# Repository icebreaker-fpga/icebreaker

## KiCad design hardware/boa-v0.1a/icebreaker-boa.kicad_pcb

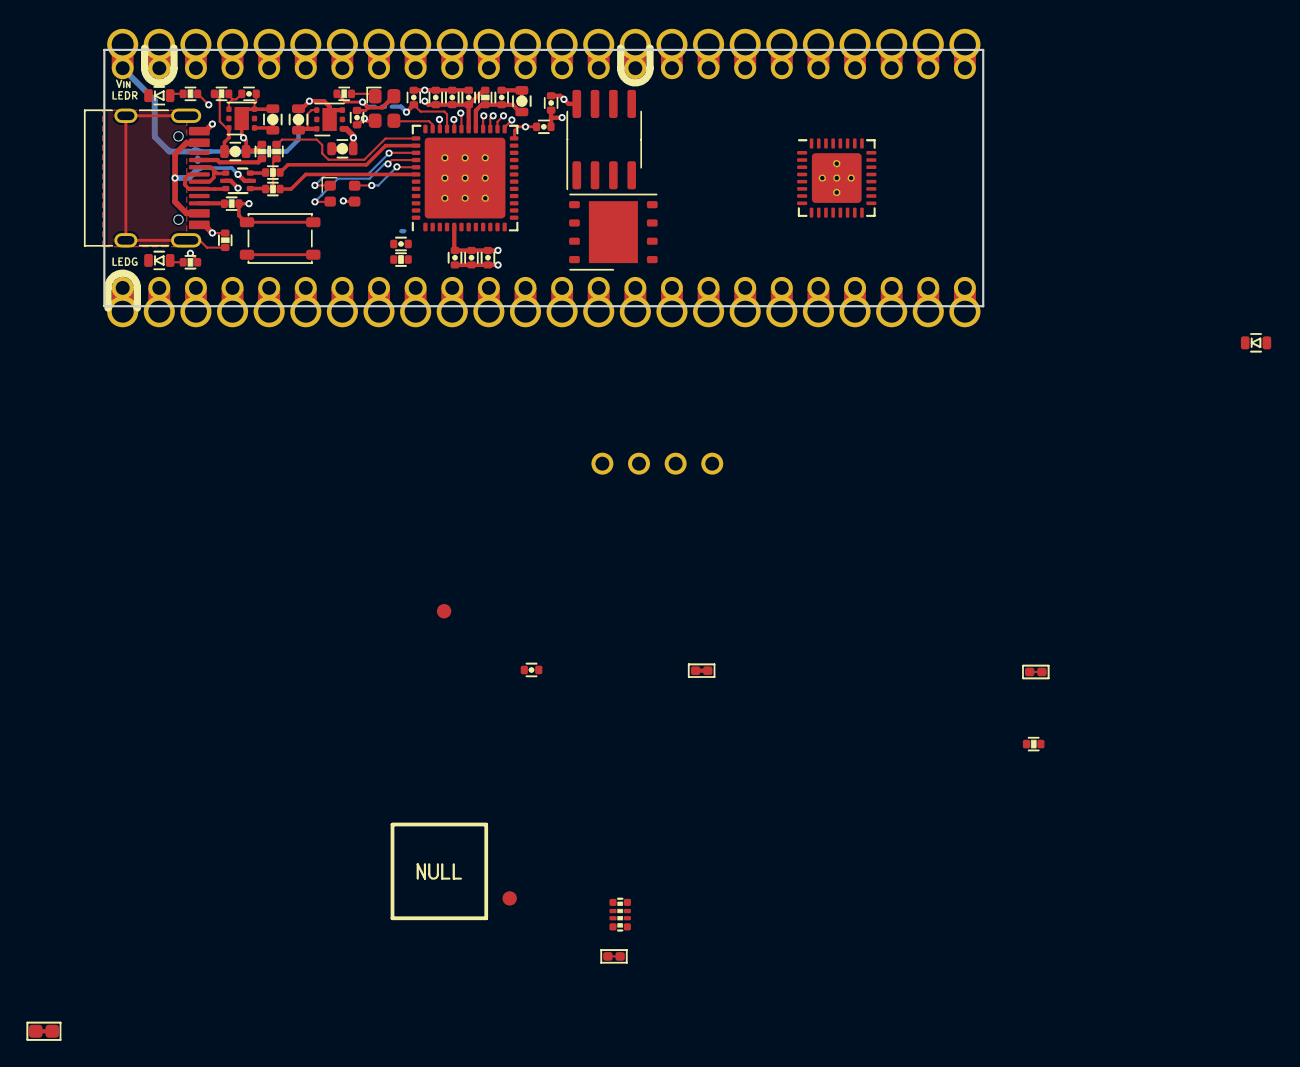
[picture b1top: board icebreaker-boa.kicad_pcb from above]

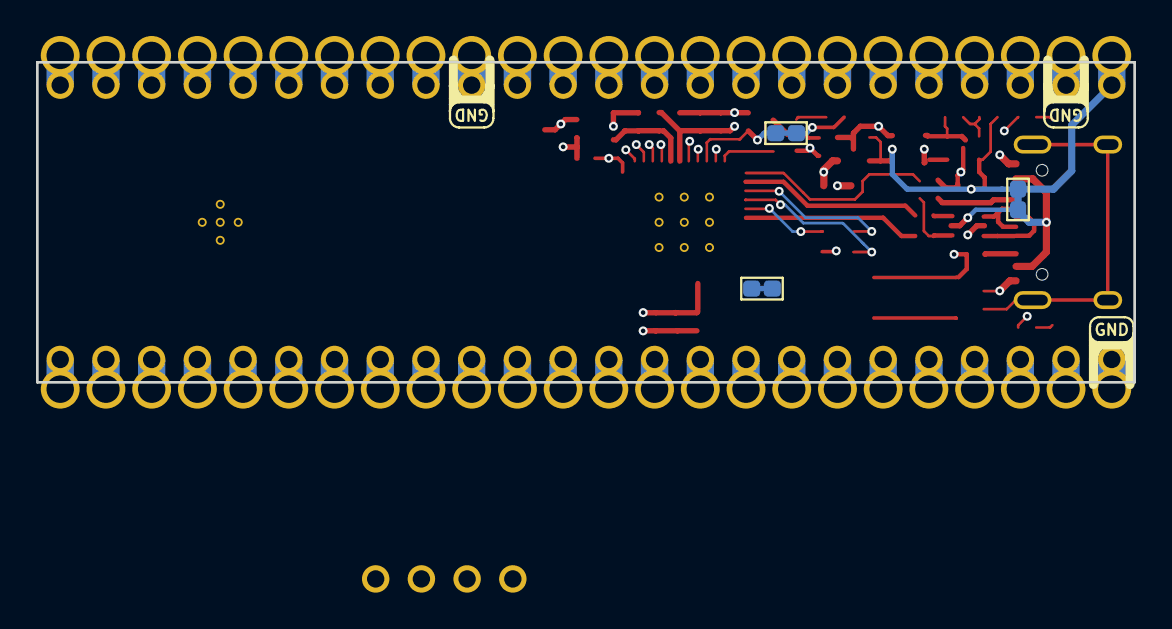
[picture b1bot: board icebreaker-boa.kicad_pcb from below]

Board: 4 copper layers, 61.0 x 17.8 mm, 109 parts (3 on the bottom side), 41 nets.

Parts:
C1, C9, C14: 1u; C_0402
C2, C3, C4, C5: 4u7; C_0603
C6, C7, C8, C11, C12, C15, C17, C18, C19: 100n; C_0402
C10: 10u; C_0603
C13, C16: 10n; C_0402
D1: RED; D_0603
D2: GRN; D_0603
D3: BLU; D_0603
D4: FM-B2020RGBA-HG; LED_TRI_2020
J1: USB_C; USB_C_Receptacle_HRO_TYPE-C-31-M-12
JP1: Jumper; J_NC_0603_40
JP2, JP3: Jumper; J_NC_0402_15
JP4, JP6, JP7: Jumper; J_NC_0603_30
JP5: Jumper; J_NC_0402_30
LOGO1: 1BitSquared; null_Logo_SilkS_6.5mm
P1, P2, P3, P4, P5, P6, P7, P8, P9, P10, P11, P12, P13, P14, P15, P16, P17, P18, P19, P20, P21, P22, P23, P24, P25, P26, P27, P28, P29, P30, P31, P32, P33, P34, P35, P42, P43, P44, P45, P46, P47, P48, P49, P50, P51, P52, P53, P54: ?; Pin_Header_Straight_Round_1x01_Castellated
P36: CS; Pin_Header_Straight_Round_1x01
P37: SCK; Pin_Header_Straight_Round_1x01
P38: MISO; Pin_Header_Straight_Round_1x01
P39: MOSI; Pin_Header_Straight_Round_1x01
P40: IO3; PAD_SMD_R_1x1
P41: IO2; PAD_SMD_R_1x1
R1: 1M; R_0402
R2, R3: 5k1; R_0402
R4, R5: 22E; R_0402
R6: 1k5; R_0402
R7, R8, R10: 10k; R_0402
R9: 10k; R_Array_Convex_4x0402
R11, R12, R13: 2k2; R_0402
R14: 100E; R_0402
SW1: TACT; SW_SPST_3x4x2.5
U1: USBLC6-2; SOT-666
U2: TLV75533PDRV; WSON-6-1EP_2x2mm_P0.65mm_EP1x1.6mm
U3: TLV73312PDRV; WSON-6-1EP_2x2mm_P0.65mm_EP1x1.6mm
U4: LY68L6400; SOIC-8_3.9x4.9mm_P1.27mm
U5: W25Q128JVxxM; WSON-8-1EP_6x5mm_P1.27mm_EP3.4x4.3mm
U6: ICE40UP5K-SG48; QFN-48-1EP_7x7mm_Pitch0.5mm
U7: ESP32-C3; QFN-32-1EP_5x5mm_Pitch0.5mm
X1: 12MHz; Oscillator_SMD_SCTF_S2DXX-4Pin_2.5x2.0mm

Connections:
+1V2: C5.1, C9.1, C11.1, C13.1, C14.1, C15.1, C16.1, R14.2, U3.1, U6.5, U6.30
+3V3: C3.1, C6.1, C7.1, C19.1, D4.3, JP4.2, JP5.1, JP6.2, JP7.2, P15.1, P50.1, R8.1, R9.1, R9.3, R9.6, R9.8, R11.2, R12.2, R13.2, U2.1, U4.8, U5.8, U6.22, U7.2, U7.3, U7.11, U7.17, U7.18, X1.4
/3V3_EN: C1.1, R7.2, U2.4
/AREF: JP7.1, U7.31, U7.32
/CC1: J1.A5, R2.2
/CC2: J1.B5, R3.2
/CDONE: D3.A, R13.1, U6.7
/CLK: U6.35, X1.3
/CLK_EN: R8.2, X1.1
/FLASH_~CS: JP3.1, R9.4, U5.1
/FPGA/VCCPLL: C10.1, C12.1, R14.1, U6.29
/FPGA/VPP_2V5: C17.1, JP5.2, U6.24
/IOB_13b-~LEDG: D2.C, JP2.2, U6.6
/IOT_36b-~LEDR: D1.C, U6.25
/RAM_~CS: JP2.1, R9.7, U4.1
/SHIELD: J1.S1, R1.2
/SPI_MISO-IO1: P38.1, U4.2, U5.2, U6.17
/SPI_MOSI-IO0: P39.1, U4.5, U5.5, U6.14
/SPI_SCK: P37.1, R9.2, U4.6, U5.6, U6.15
/SPI_~CS: JP3.2, P36.1, U6.16
/SPI_~HLD~-IO3: P40.1, U4.7, U5.7, U6.19
/SPI_~WP~-IO2: P41.1, U4.3, U5.3, U6.18
/USB_DET: R6.1, U6.37
/USB_N: R4.1, U6.38
/USB_P: R5.1, U6.42
/VCCIO_0: C18.1, JP6.1, U6.33
/VCCIO_2: C8.1, JP4.1, R10.2, U6.1
/iD+: R5.2, R6.2, U1.4
/iD-: R4.2, U1.6
/xD+: J1.A6, J1.B6, U1.3
/xD-: J1.A7, J1.B7, U1.1
/~BTN: R10.1, SW1.2, U6.2
/~CRESET: R9.5, U6.8
/~RGB0: D4.1, U6.39
/~RGB1: D4.4, U6.40
/~RGB2: D4.2, U6.41
GND: C1.2, C2.2, C3.2, C4.2, C5.2, C6.2, C7.2, C8.2, C9.2, C10.2, C11.2, C12.2, C13.2, C14.2, C15.2, C16.2, C17.2, C18.2, C19.2, D3.C, J1.A1, J1.A12, J1.B1, J1.B12, P1.1, P46.1, P53.1, R1.1, R2.1, R3.1, SW1.1, U1.2, U2.3, U2.7, U3.3, U3.7, U4.4, U5.4, U6.49, U7.33, X1.2
unnamed: D1.A, R11.1
unnamed: D2.A, R12.1
VBUS: J1.A4, J1.A9, J1.B4, J1.B9, JP1.1, U1.5
VIN: C2.1, C4.1, JP1.2, P4.1, R7.1, U2.6, U3.4, U3.6

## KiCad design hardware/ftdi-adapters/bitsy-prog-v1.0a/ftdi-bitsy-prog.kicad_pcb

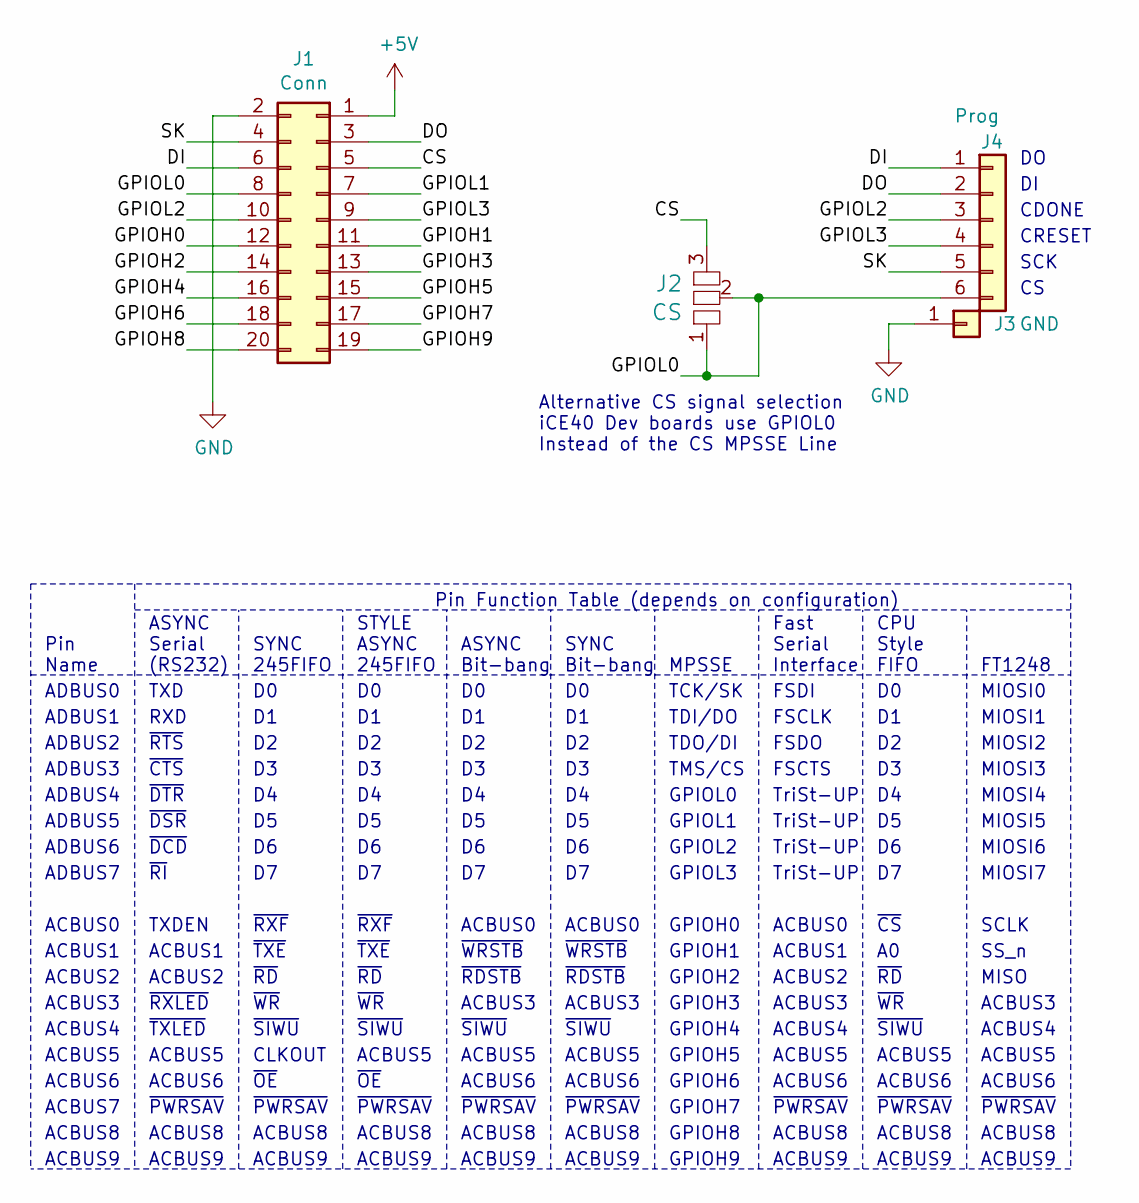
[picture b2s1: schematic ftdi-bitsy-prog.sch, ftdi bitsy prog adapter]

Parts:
J1: Conn; FTSH-EDGE-20pin
J2: CS; J_0602
J3: GND; PinSocket_1x01_P2.54mm_Vertical
J4: Prog; PinSocket_1x06_P2.54mm_Vertical

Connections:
+5V: J1.1
/CS: J1.5, J2.3
/DI: J1.6, J4.1
/DO: J1.3, J4.2
/GPIOH0: J1.12
/GPIOH1: J1.11
/GPIOH2: J1.14
/GPIOH3: J1.13
/GPIOH4: J1.16
/GPIOH5: J1.15
/GPIOH6: J1.18
/GPIOH7: J1.17
/GPIOH8: J1.20
/GPIOH9: J1.19
/GPIOL0: J1.8, J2.1, J2.2, J4.6
/GPIOL1: J1.7
/GPIOL2: J1.10, J4.3
/GPIOL3: J1.9, J4.4
/SK: J1.4, J4.5
GND: J1.2, J3.1

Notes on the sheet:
STYLE ASYNC 245FIFO
~RXF
~TXE
~RD
~WR
~SIWU
ACBUS5
~OE
~PWRSAV
ACBUS8
ACBUS9
ASYNC Bit-bang
ACBUS0
~WRSTB
~RDSTB
ACBUS3
ACBUS6
SYNC Bit-bang
MPSSE
TCK/SK
TDI/DO
TDO/DI
TMS/CS
GPIOL0
GPIOL1
GPIOL2
GPIOL3
GPIOH0
GPIOH1
GPIOH2
GPIOH3
GPIOH4
GPIOH5
GPIOH6
GPIOH7
GPIOH8
GPIOH9
Fast Serial Interface
FSDI
FSCLK

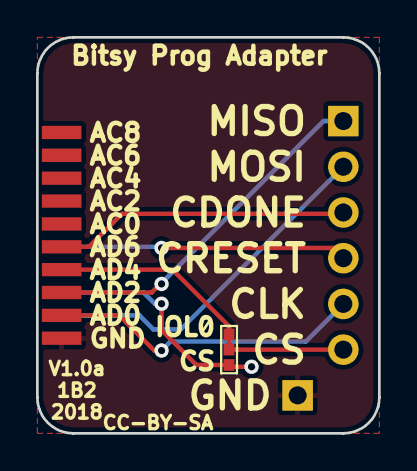
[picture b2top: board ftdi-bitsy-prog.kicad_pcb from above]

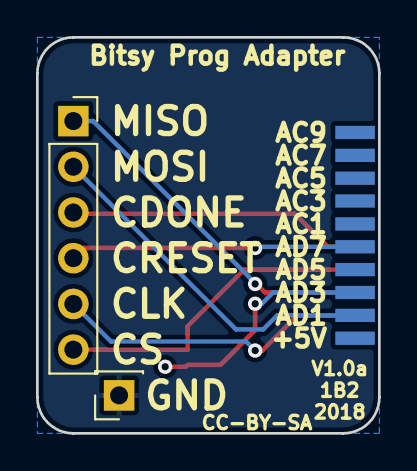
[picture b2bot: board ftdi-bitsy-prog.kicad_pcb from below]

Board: 2 copper layers, 19.0 x 22.0 mm, 4 parts (3 on the bottom side), 8 nets.

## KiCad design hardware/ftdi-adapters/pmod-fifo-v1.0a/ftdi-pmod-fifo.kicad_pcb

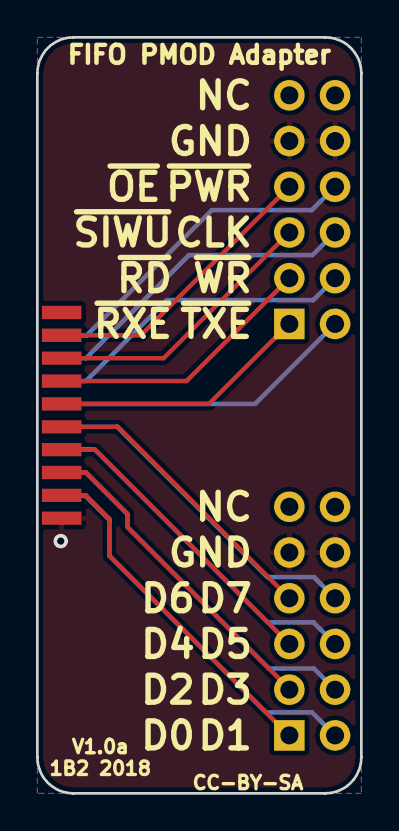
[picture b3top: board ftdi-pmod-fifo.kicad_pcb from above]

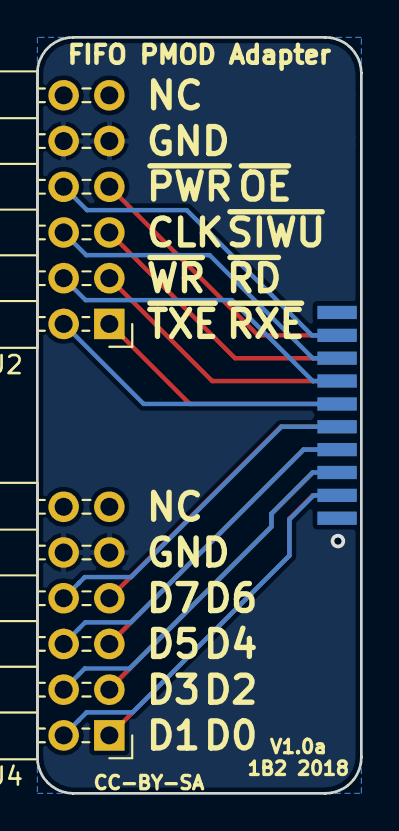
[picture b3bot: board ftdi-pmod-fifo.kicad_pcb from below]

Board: 2 copper layers, 18.0 x 42.0 mm, 3 parts (3 on the bottom side), 17 nets.

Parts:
J1: Conn; FTSH-EDGE-20pin
J2, J4: PMOD; PinHeader_2x06_P2.54mm_Horizontal

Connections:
/CLKOUT: J1.15, J2.6
/D0: J1.4, J4.1
/D1: J1.3, J4.2
/D2: J1.6, J4.3
/D3: J1.5, J4.4
/D4: J1.8, J4.5
/D5: J1.7, J4.6
/D6: J1.10, J4.7
/D7: J1.9, J4.8
/~OE: J1.18, J2.7
/~PWRSAV: J1.17, J2.8
/~RD: J1.14, J2.3
/~RXF: J1.12, J2.1
/~SIWU: J1.16, J2.5
/~TXE: J1.11, J2.2
/~WR: J1.13, J2.4
GND: J1.2, J2.9, J2.10, J4.9, J4.10

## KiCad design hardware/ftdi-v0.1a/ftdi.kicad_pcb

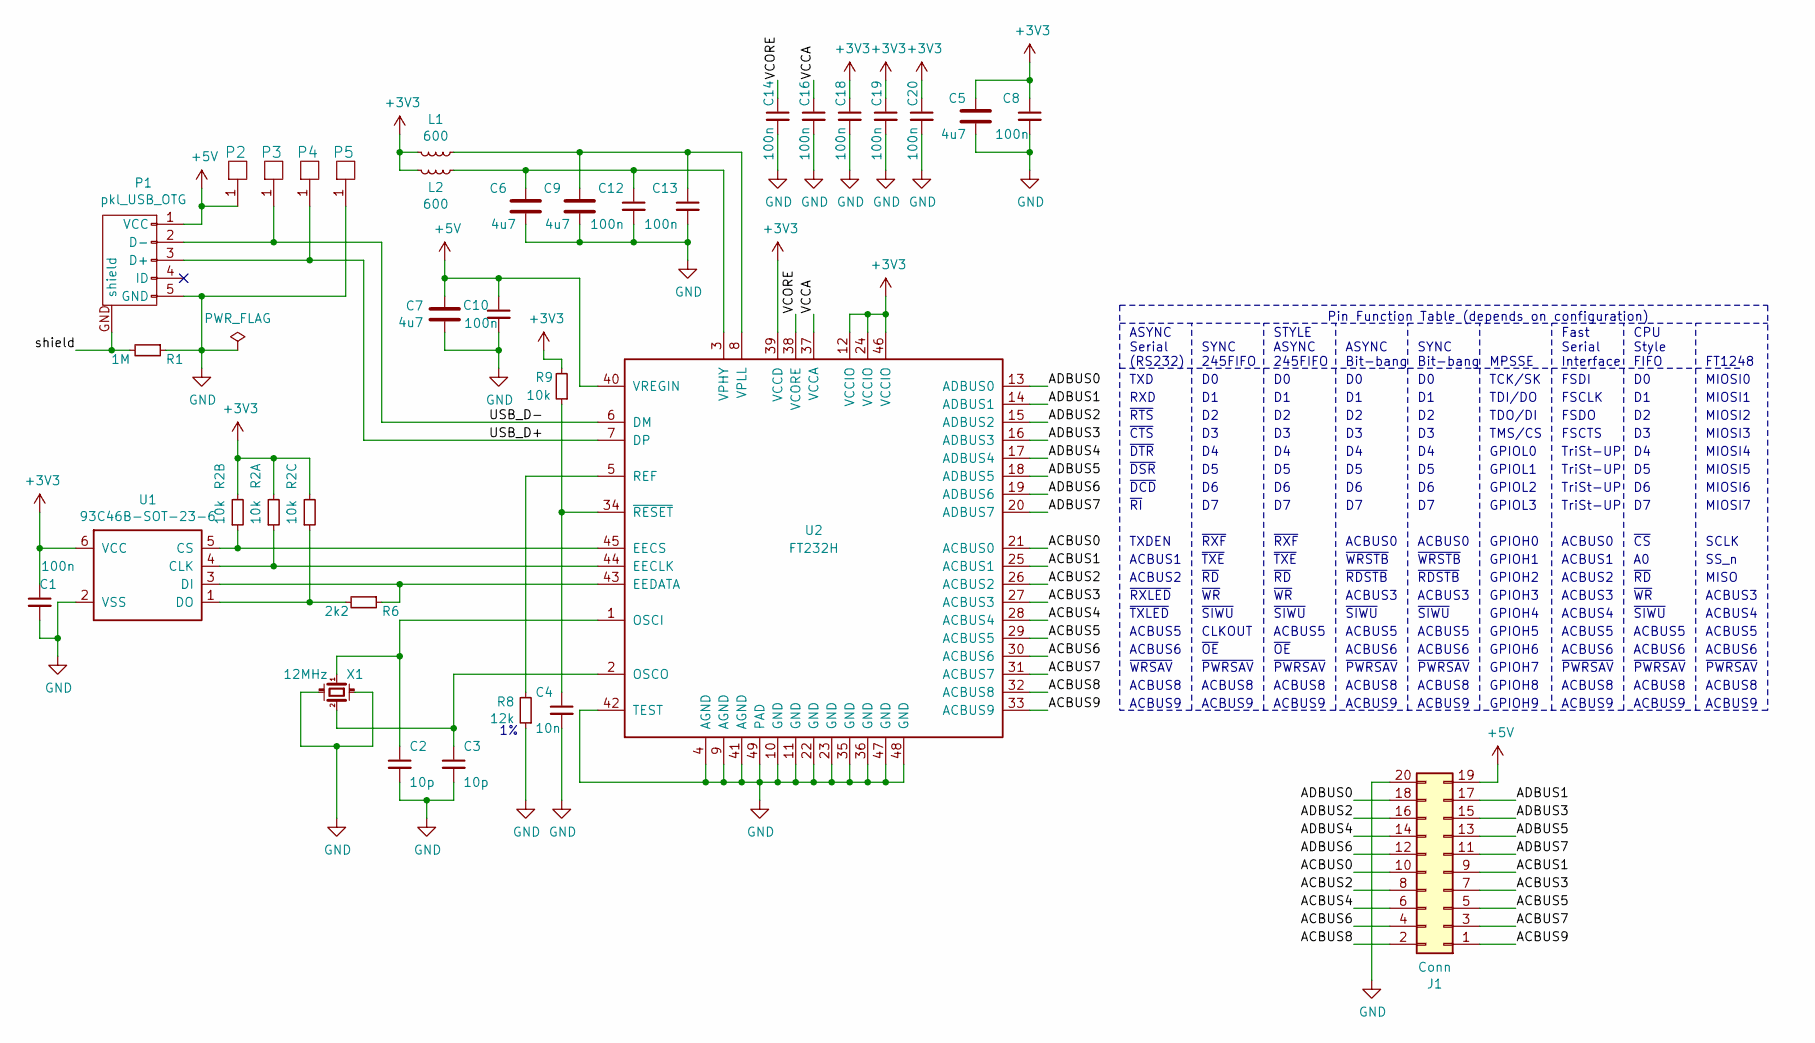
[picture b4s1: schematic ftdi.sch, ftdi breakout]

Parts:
C1, C8, C10, C12, C13, C14, C16, C18, C19, C20: 100n; C_0402
C2, C3: 10p; C_0402
C4: 10n; C_0402
C5, C6, C7, C9: 4u7; C_0603
J1: Conn; FTSH-EDGE-20pin
L1, L2: 600; L_0402
P1: pkl_USB_OTG; Connector_USB_Micro_B_SMD
P2, P3, P4, P5: UP; PAD_SMD_1x2.65
R1: 1M; R_0402
R2: 10k; R_Array_Convex_4x0402
R6: 2k2; R_0402
R8: 12k; R_0402
R9: 10k; R_0402
U1: 93C46B-SOT-23-6; SOT-23-6
U2: FT232H; QFN-48-1EP_8x8mm_Pitch0.5mm
X1: 12MHz; ABM8

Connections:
+3V3: C1.1, C5.1, C8.1, C18.1, C19.1, C20.1, L1.1, L2.1, R2.2, R2.4, R2.6, R9.2, U1.6 (VCC), U2.12 (VCCIO), U2.24 (VCCIO), U2.39 (VCCD), U2.46 (VCCIO)
+5V: C7.1, C10.1, J1.19, P1.1 (VCC), P2.1, U2.40 (VREGIN)
/ACBUS0: J1.10, U2.21 (ACBUS0)
/ACBUS1: J1.9, U2.25 (ACBUS1)
/ACBUS2: J1.8, U2.26 (ACBUS2)
/ACBUS3: J1.7, U2.27 (ACBUS3)
/ACBUS4: J1.6, U2.28 (ACBUS4)
/ACBUS5: J1.5, U2.29 (ACBUS5)
/ACBUS6: J1.4, U2.30 (ACBUS6)
/ACBUS7: J1.3, U2.31 (ACBUS7)
/ACBUS8: J1.2, U2.32 (ACBUS8)
/ACBUS9: J1.1, U2.33 (ACBUS9)
/ADBUS0: J1.18, U2.13 (ADBUS0)
/ADBUS1: J1.17, U2.14 (ADBUS1)
/ADBUS2: J1.16, U2.15 (ADBUS2)
/ADBUS3: J1.15, U2.16 (ADBUS3)
/ADBUS4: J1.14, U2.17 (ADBUS4)
/ADBUS5: J1.13, U2.18 (ADBUS5)
/ADBUS6: J1.12, U2.19 (ADBUS6)
/ADBUS7: J1.11, U2.20 (ADBUS7)
/USB_D+: P1.3 (D+), P4.1, U2.7 (DP)
/USB_D-: P1.2 (D-), P3.1, U2.6 (DM)
/VCCA: C16.1, U2.37 (VCCA)
/VCORE: C14.1, U2.38 (VCORE)
/shield: P1.GND (shield), R1.2
GND: C1.2, C2.2, C3.2, C4.2, C5.2, C6.2, C7.2, C8.2, C9.2, C10.2, C12.2, C13.2, C14.2, C16.2, C18.2, C19.2, C20.2, J1.20, P1.5 (GND), P5.1, R1.1, R8.1, U1.2 (VSS), U2.4 (AGND), U2.9 (AGND), U2.10 (GND), U2.11 (GND), U2.22 (GND), U2.23 (GND), U2.35 (GND), U2.36 (GND), U2.41 (AGND), U2.42 (TEST), U2.47 (GND), U2.48 (GND), U2.49 (PAD), X1.GND (case)
unnamed: C2.1, U2.1 (OSCI), X1.1
unnamed: C3.1, U2.2 (OSCO), X1.2
unnamed: C4.1, R9.1, U2.34 (~RESET)
unnamed: C6.1, C12.1, L2.2, U2.3 (VPHY)
unnamed: C9.1, C13.1, L1.2, U2.8 (VPLL)
unnamed: R2.1, U1.4 (CLK), U2.44 (EECLK)
unnamed: R2.3, U1.5 (CS), U2.45 (EECS)
unnamed: R2.5, R6.2, U1.1 (DO)
unnamed: R6.1, U1.3 (DI), U2.43 (EEDATA)
unnamed: R8.2, U2.5 (REF)

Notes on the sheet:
ASYNC Serial (RS232)
TXD
RXD
~RTS
~CTS
~DTR
~DSR
~RI
~DCD
TXDEN
ACBUS1
ACBUS2
~RXLED
~TXLED
ACBUS5
ACBUS6
~WRSAV
ACBUS8
ACBUS9
SYNC 245FIFO
~RXF
~TXE
~RD
~WR
~SIWU
CLKOUT
~OE
~PWRSAV
STYLE ASYNC 245FIFO
ASYNC Bit-bang
ACBUS0
~WRSTB
~RDSTB
ACBUS3
SYNC Bit-bang
MPSSE
TCK/SK
TDI/DO
TDO/DI
TMS/CS

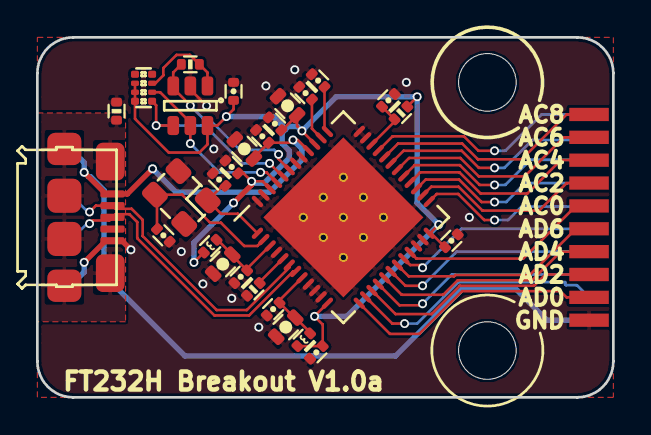
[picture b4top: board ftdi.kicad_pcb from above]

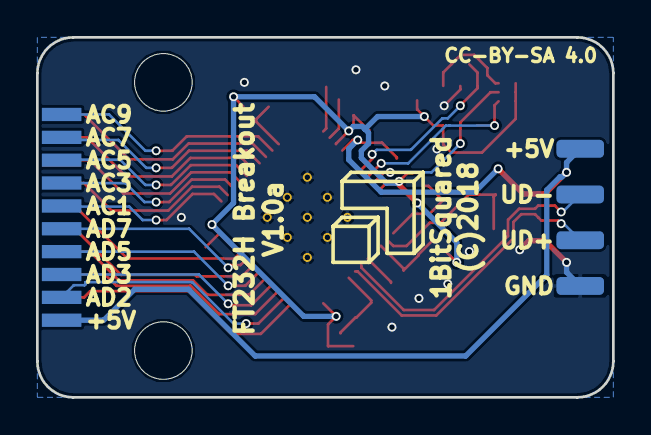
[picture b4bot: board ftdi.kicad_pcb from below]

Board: 2 copper layers, 32.0 x 20.0 mm, 33 parts (5 on the bottom side), 36 nets.

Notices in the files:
hardware/boa-v0.1a/icebreaker-boa.kicad_pcb:
© 2018-2020 1BitSquared
© 2018-2020 Piotr Esden-Tempski
© 2020 Jordi Pakey-Rodriguez
License: CC BY-SA 4.0
hardware/ftdi-adapters/bitsy-prog-v1.0a/ftdi-bitsy-prog.kicad_pcb:
CC-BY-SA
hardware/ftdi-v0.1a/ftdi.kicad_pcb:
(C) 2018 Piotr Esden-Tempski
(C) 2018 1BitSquared
CC-BY-SA 4.0
(C)2018
hardware/ftdi-v0.1a/ftdi.sch:
License: CC-BY-SA V4.0
